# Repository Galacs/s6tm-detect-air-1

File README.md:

# S6TM Detect air 1

Air module 1 for the detect series with various co2 and mox air sensors

## IC List

- STM32F103C8T6 (Main MCU)
- HT7533 (MCU 3v3 LDO)
- HTU21D (Temperature and humidity)
- MiCS-5524 (MOX air sensor)
- S88 (CO2 NDIR sensor)
- ENS160 (MOX Sensor)
- SGP41 (MOX Sensors)
- SCD41 ("NDIR" co2 sensor)
- LMC6482 (op amp)
- SN65HVD230DR (CAN transceiver)
- LM73100 (+5V input protection)

## Top preview

## Preview 3d render

## Pin definitions

```c
#define I2C_SCL_PIN PB6
#define I2C_SDA_PIN PB7

#define RS1_PIN PA5
#define RS2_PIN PA6

#define CAN_RX_PIN PB8
#define CAN_RX_PIN  PB9

#define S88_TX_PIN PA10
#define S88_RX_PIN PA9

#define ENS160_INT_PIN PA15
```

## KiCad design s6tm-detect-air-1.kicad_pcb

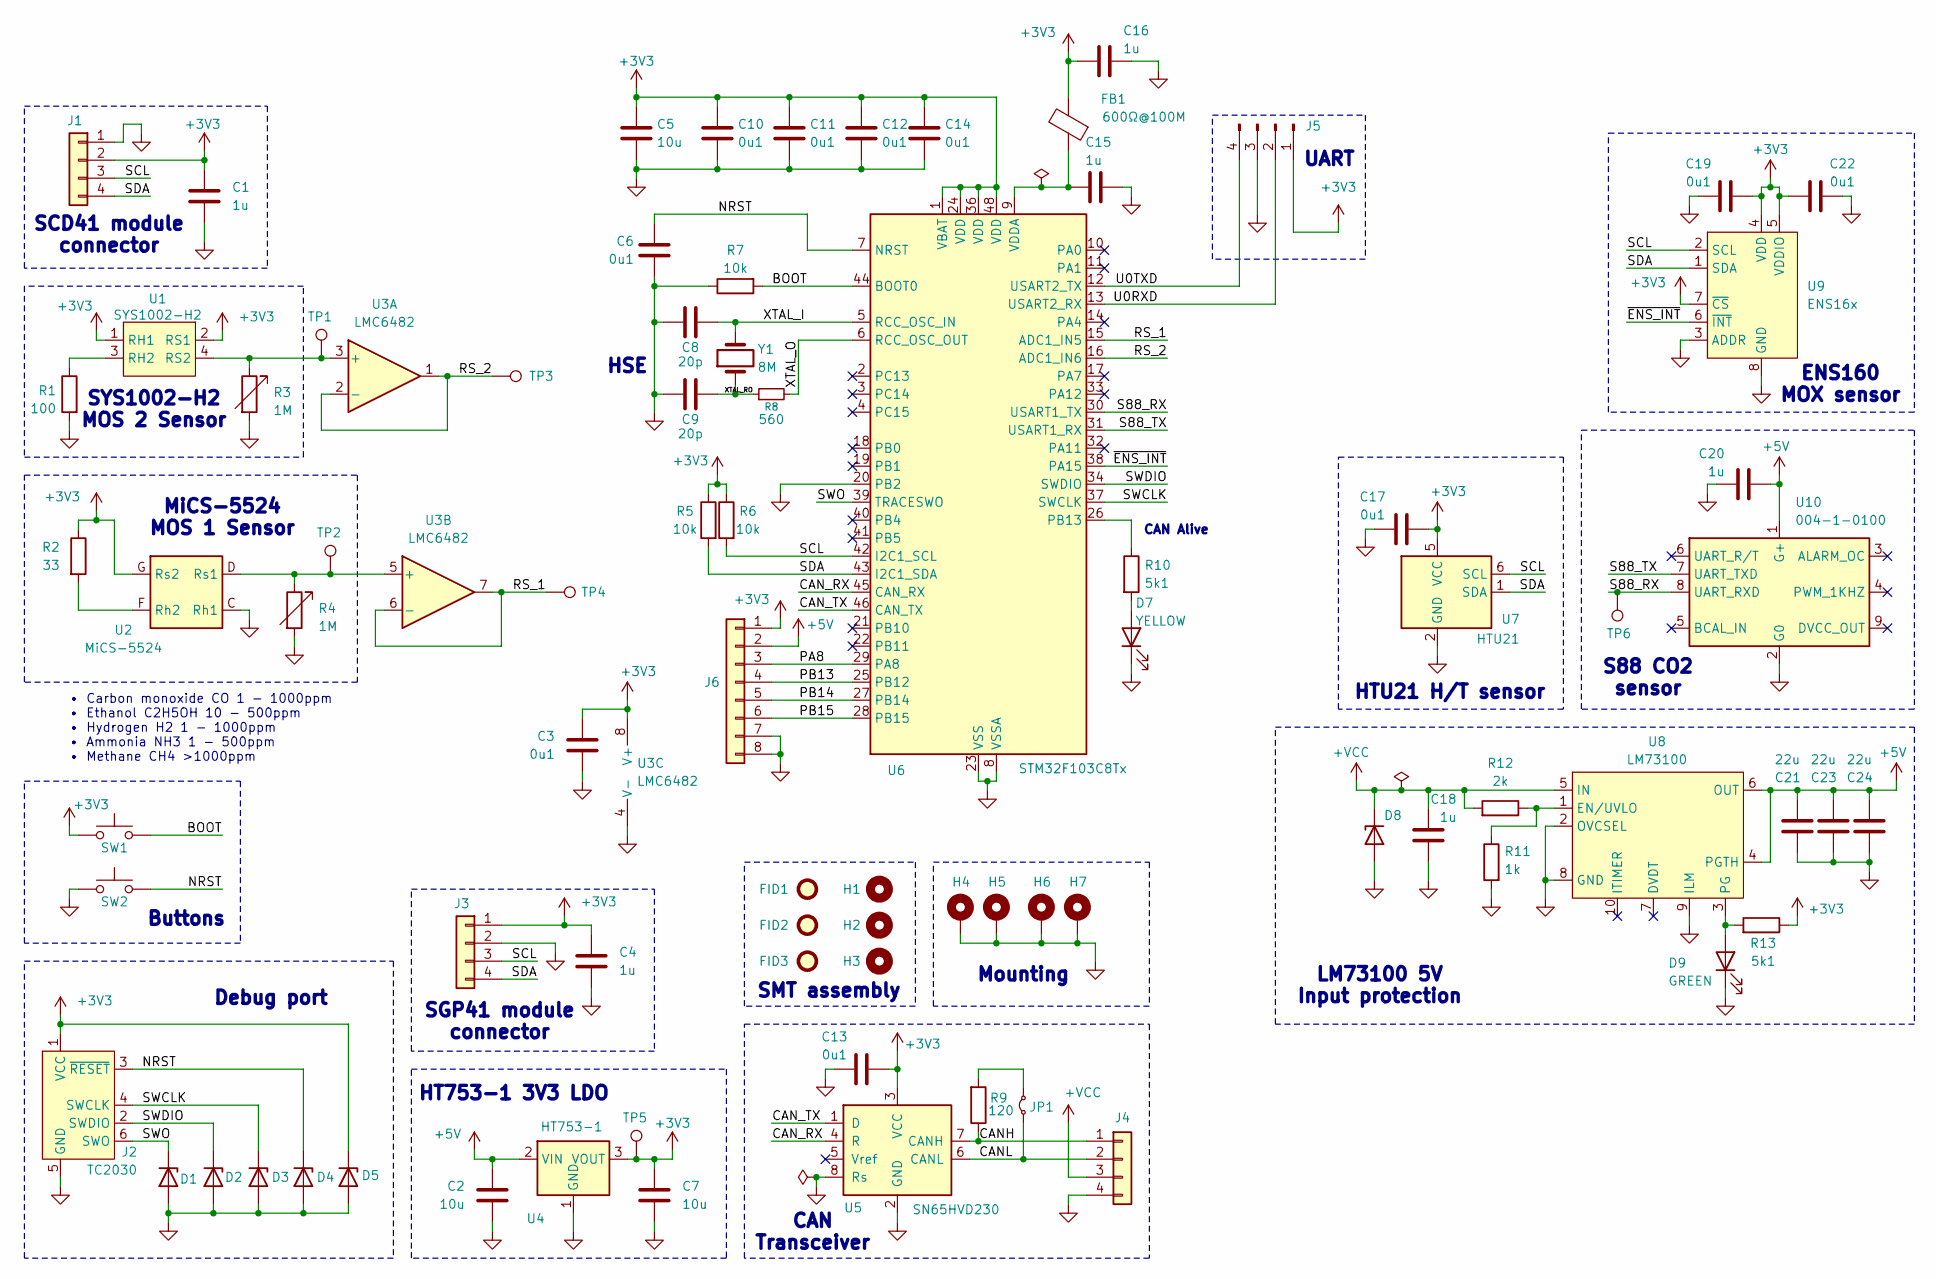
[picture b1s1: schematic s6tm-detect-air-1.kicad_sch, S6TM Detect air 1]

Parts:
C1, C4, C15, C16, C18, C20: 1u; C_0402_1005Metric; Manufacturer Part Number CL05A105KA5NQNC; JLCPCB Part # C52923
C2, C5, C7: 10u; C_0805_2012Metric; Manufacturer Part Number GRM21BR61H106KE43L; JLCPCB Part # C440198
C3, C6, C10, C11, C12, C13, C14, C17, C19, C22: 0u1; C_0402_1005Metric; Manufacturer Part Number CL05B104KB54PNC; JLCPCB Part # C307331
C8, C9: 20p; C_0603_1608Metric; Manufacturer Part Number CL10C200JB8NNNC; JLCPCB Part # C1648
C21, C23, C24: 22u; C_0805_2012Metric; Manufacturer Part Number CL21A226MAQNNNE; JLCPCB Part # C45783
D1, D2, D3, D4, D5: H5VU10U; Diode_DFN1006; Manufacturer Part Number H5VU10U; JLCPCB Part # C22395519
D7: YELLOW; LED_0805_2012Metric; Manufacturer Part Number KT-0805Y; JLCPCB Part # C2296
D8: SMAJ12A; D_SMA; Manufacturer Part Number SMAJ12A; JLCPCB Part # C19077531
D9: GREEN; LED_0805_2012Metric; Manufacturer Part Number KT-0805G; JLCPCB Part # C2297
FB1: 600Ω@100M; L_0805_2012Metric; Manufacturer Part Number MPZ2012S601ATD25; JLCPCB Part # C81034
FID1, FID2, FID3: Fiducial; Fiducial_1mm_Mask2mm
H1, H2, H3: MountingHole; ToolingHole_1.152mm
H4, H5, H6, H7: MountingHole_Pad; MountingHole_3.2mm_M3_Pad_Via
J1, J3: Conn_01x04; PinHeader_1x04_P2.54mm_Vertical
J2: TC2030; Tag-Connect_TC2030-IDC-NL_2x03_P1.27mm_Vertical
J4: Conn_01x04; JST_XH_S4B-XH-A-1_1x04_P2.50mm_Horizontal; Manufacturer Part Number S4B-XH-A-1(LF)(SN); JLCPCB Part # C163037
J5: Conn_01x04_Pin; PinHeader_1x04_P2.54mm_Vertical
J6: Conn_01x08; PinHeader_2x04_P2.54mm_Horizontal
JP1: Jumper_2_Small_Bridged; SolderJumper-2_P1.3mm_Open_RoundedPad1.0x1.5mm
R1: 100; R_0402_1005Metric; Manufacturer Part Number 0402WGF1000TCE; JLCPCB Part # C25076
R2: 33; R_0603_1608Metric; Manufacturer Part Number 0603WAF330JT5E; JLCPCB Part # C23140
R3, R4: 1M; Potentiometer_Bourns_3296W_Vertical
R5, R6, R7: 10k; R_0402_1005Metric; Manufacturer Part Number 0402WGF1002TCE; JLCPCB Part # C25744
R8: 560; R_0603_1608Metric; Manufacturer Part Number 0603WAF5600T5E; JLCPCB Part # C23204
R9: 120; R_1206_3216Metric; Manufacturer Part Number 1206W4F1200T5E; JLCPCB Part # C17909
R10, R13: 5k1; R_0402_1005Metric; Manufacturer Part Number 0402WGF5101TCE; JLCPCB Part # C25905
R11: 1k; R_0402_1005Metric; Manufacturer Part Number 0402WGF1001TCE; JLCPCB Part # C11702
R12: 2k; R_0402_1005Metric; Manufacturer Part Number 0402WGF2001TCE; JLCPCB Part # C4109
SW1, SW2: SW_Push; SW_SPST_TS-1088-xR020; Manufacturer Part Number TS-1088-AR02016; JLCPCB Part # C720477
TP1, TP2, TP3, TP4, TP5, TP6: TestPoint; TestPoint_Pad_D2.0mm
U1: SYS1002-H2; Crystal_SMD_3225-4Pin_3.2x2.5mm; Manufacturer Part Number SYS1002-H2; JLCPCB Part # C5184223
U2: MiCS-5524; Sensortech_MiCS_5x7mm_P1.25mm; Manufacturer Part Number MICS-5524; JLCPCB Part # C3659348
U3: LMC6482; SOIC-8_3.9x4.9mm_P1.27mm; Manufacturer Part Number LMC6482IMX/NOPB; JLCPCB Part # C95583
U4: HT753-1; SOT-89-3; Manufacturer Part Number HT7533-1; JLCPCB Part # C14289
U5: SN65HVD230; SOIC-8_3.9x4.9mm_P1.27mm; Manufacturer Part Number SN65HVD230DR; JLCPCB Part # C12084
U6: STM32F103C8Tx; LQFP-48_7x7mm_P0.5mm; Manufacturer Part Number STM32F103C8T6; JLCPCB Part # C8734
U7: HTU21; Texas_PWSON-N6; Manufacturer Part Number HTU21D; JLCPCB Part # C83479
U8: LM73100; Texas_RPW0010A_VQFN-HR-10_2x2mm_P0.5mm; Manufacturer Part Number LM73100RPWR; JLCPCB Part # C3210761
U9: ENS16x; Sciosense_ENS160_LGA_9_3x3mm; Manufacturer Part Number ENS160-BGLM; JLCPCB Part # C3659288
U10: 004-1-0100; Senseair_S8_Up
Y1: 8M; Crystal_SMD_5032-2Pin_5.0x3.2mm; Manufacturer Part Number X50328MSB2GI; JLCPCB Part # C115962

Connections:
+3V3: C1.2, C3.2, C4.2, C5.1, C7.1, C10.1, C11.1, C12.1, C13.1, C14.1, C16.1, C17.2, C19.1, C22.1, D5.1 (K), FB1.2, J1.2, J2.1 (VCC), J3.1, J5.1, J6.1, R2.1, R5.1, R6.1, R13.1, SW1.1, TP5.1 (1_1), U1.1 (RH1), U1.2 (RS1), U2.G (Rs2), U3.8 (V+), U4.3 (VOUT), U5.3 (VCC), U6.1 (VBAT), U6.24 (VDD), U6.36 (VDD), U6.48 (VDD), U7.5 (VCC), U9.4 (VDD), U9.5 (VDDIO), U9.7 (~CS)
+5V: C2.1, C20.1, C21.2, C23.2, C24.2, J6.2, U4.2 (VIN), U8.4 (PGTH), U8.6 (OUT), U10.1 (G+)
+VCC: C18.2, D8.1 (K), J4.3, R12.2, U8.5 (IN)
/BOOT: R7.2, SW1.2, U6.44 (BOOT0)
/CANH: J4.1, R9.1, U5.7 (CANH)
/CANL: J4.2, JP1.1 (A), U5.6 (CANL)
/CAN_RX: U5.4 (R), U6.45 (CAN_RX)
/CAN_TX: U5.1 (D), U6.46 (CAN_TX)
/NRST: C6.1, D4.1 (K), J2.3 (~RESET), SW2.2, U6.7 (NRST)
/PA8: J6.3, U6.29 (PA8)
/PB13: J6.4, U6.25 (PB12)
/PB14: J6.5, U6.27 (PB14)
/PB15: J6.6, U6.28 (PB15)
/RS_1: TP4.1 (1_1), U3.6 (-), U3.7, U6.15 (ADC1_IN5)
/RS_2: TP3.1 (1_1), U3.1, U3.2 (-), U6.16 (ADC1_IN6)
/S88_RX: TP6.1 (1_1), U6.30 (USART1_TX), U10.8 (UART_RXD)
/S88_TX: U6.31 (USART1_RX), U10.7 (UART_TXD)
/SCL: J1.3, J3.3, R6.2, U6.42 (I2C1_SCL), U7.6 (SCL), U9.2 (SCL)
/SDA: J1.4, J3.4, R5.2, U6.43 (I2C1_SDA), U7.1 (SDA), U9.1 (SDA)
/SWCLK: D3.1 (K), J2.4 (SWCLK), U6.37 (SWCLK)
/SWDIO: D2.1 (K), J2.2 (SWDIO), U6.34 (SWDIO)
/SWO: D1.1 (K), J2.6 (SWO), U6.39 (TRACESWO)
/U0RXD: J5.2, U6.13 (USART2_RX)
/U0TXD: J5.4, U6.12 (USART2_TX)
/XTAL_I: C8.1, U6.5 (RCC_OSC_IN), Y1.2
/XTAL_O: R8.2, U6.6 (RCC_OSC_OUT)
/XTAL_RO: C9.1, R8.1, Y1.1
/~ENS_INT: U6.38 (PA15), U9.6 (~INT)
GND: C1.1, C2.2, C3.1, C4.1, C5.2, C6.2, C7.2, C8.2, C9.2, C10.2, C11.2, C12.2, C13.2, C14.2, C15.2, C16.2, C17.1, C18.1, C19.2, C20.2, C21.1, C22.2, C23.1, C24.1, D1.2 (A), D2.2 (A), D3.2 (A), D4.2 (A), D5.2 (A), D7.1 (K), D8.2 (A), D9.1 (K), H4.1 (1_1), H5.1 (1_1), H6.1 (1_1), H7.1 (1_1), J1.1, J2.5 (GND), J3.2, J4.4, J5.3, J6.7, J6.8, R1.2, R3.2, R4.2, R7.1, R11.2, SW2.1, U2.C (Rh1), U3.4 (V-), U4.1 (GND), U5.2 (GND), U5.8 (Rs), U6.8 (VSSA), U6.20 (PB2), U6.23 (VSS), U6.35 (VSS), U6.47 (VSS), U7.2 (GND), U8.2 (OVCSEL), U8.8 (GND), U8.9 (ILM), U9.3 (ADDR), U9.8 (GND), U9.9 (GND), U10.2 (G0)
unnamed: D7.2 (A), R10.2
unnamed: D9.2 (A), R13.2, U8.3 (PG)
unnamed: JP1.2 (B), R9.2
unnamed: R1.1, U1.3 (RH2)
unnamed: R3.1, TP1.1 (1_1), U1.4 (RS2), U3.3 (+)
unnamed: R2.2, U2.F (Rh2)
unnamed: R4.1, TP2.1 (1_1), U2.D (Rs1), U3.5 (+)
unnamed: R10.1, U6.26 (PB13)
unnamed: C15.1, FB1.1, U6.9 (VDDA)
unnamed: R11.1, R12.1, U8.1 (EN/UVLO)

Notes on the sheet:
CAN Transceiver
SCD41 module connector
Mounting
SYS1002-H2 MOS 2 Sensor
SMT assembly
MiCS-5524 MOS 1 Sensor
HTU21 H/T sensor
LM73100 5V Input protection
Buttons
SGP41 module connector
UART
• Carbon monoxide CO 1 - 1000ppm • Ethanol C2H5OH 10 - 500ppm • Hydrogen H2 1 - 1000ppm • Ammonia NH3 1 - 500ppm • Methane CH4 >1000ppm
HSE
ENS160 MOX sensor
S88 CO2 sensor
CAN Alive
Debug port
HT753-1 3V3 LDO

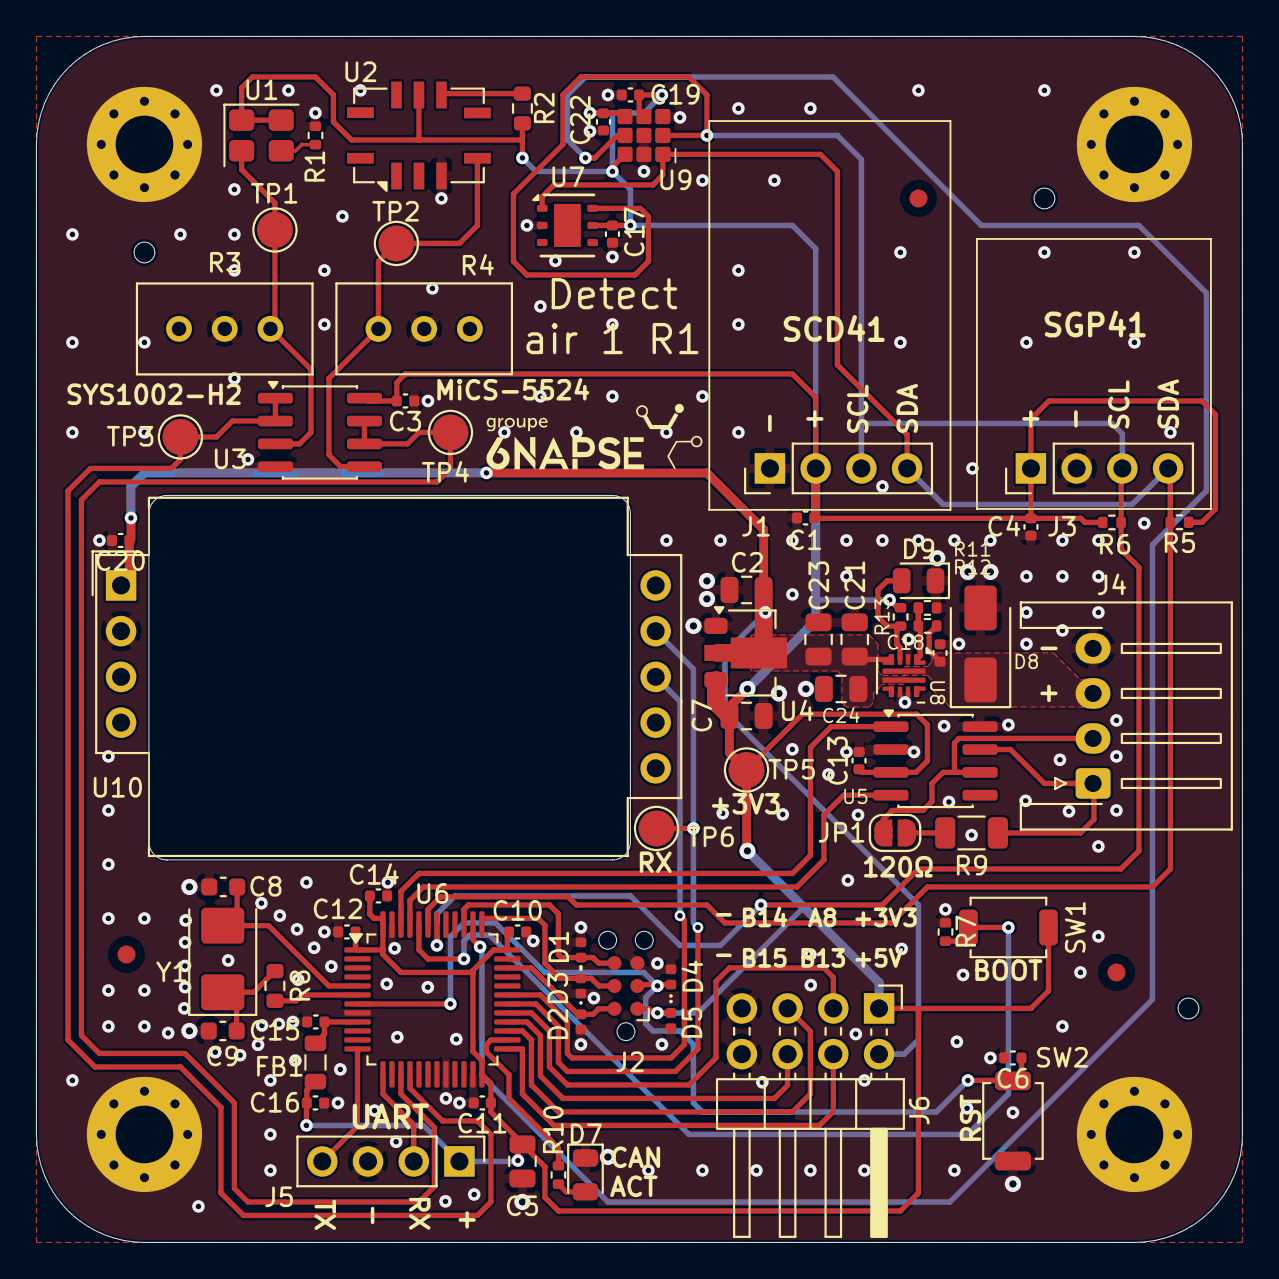
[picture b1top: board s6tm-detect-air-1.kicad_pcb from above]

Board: 2 copper layers, 67.0 x 67.0 mm, 82 parts (0 on the bottom side), 39 nets.

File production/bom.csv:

Designator,Footprint,Quantity,Value,LCSC Part #
"C1, C15, C16, C18, C20, C4",0402,6,1u,C52923
"C10, C11, C12, C13, C14, C17, C19, C22, C3, C6",0402,10,0u1,C307331
"C2, C5, C7",0805,3,10u,C440198
"C21, C23, C24",0805,3,22u,C45783
"C8, C9",0603,2,20p,C1648
"D1, D2, D3, D4, D5",Diode_DFN1006,5,H5VU10U,C22395519
D7,0805,1,YELLOW,C2296
D8,D_SMA,1,SMAJ12A,C19077531
D9,0805,1,GREEN,C2297
FB1,0805,1,600Ω@100M,C81034
J6,PinHeader_2x04_P2.54mm_Horizontal,1,Conn_01x08,
R1,0402,1,100,C25076
"R10, R13",0402,2,5k1,C25905
R11,0402,1,1k,C11702
R12,0402,1,2k,C4109
R2,0603,1,33,C23140
"R5, R6, R7",0402,3,10k,C25744
R8,0603,1,560,C23204
R9,1206,1,120,C17909
"SW1, SW2",SW_SPST_TS-1088-xR020,2,SW_Push,C720477
U1,Crystal_SMD_3225-4Pin_3.2x2.5mm,1,SYS1002-H2,C5184223
U2,Sensortech_MiCS_5x7mm_P1.25mm,1,MiCS-5524,C3659348
U3,SOIC-8_3.9x4.9mm_P1.27mm,1,LMC6482,C95583
U4,SOT-89-3,1,HT753-1,C14289
U5,SOIC-8_3.9x4.9mm_P1.27mm,1,SN65HVD230,C12084
U6,LQFP-48_7x7mm_P0.5mm,1,STM32F103C8Tx,C8734
U7,Texas_PWSON-N6,1,HTU21,C83479
U8,Texas_RPW0010A_VQFN-HR-10_2x2mm_P0.5mm,1,LM73100,C3210761
U9,Sciosense_ENS160_LGA_9_3x3mm,1,ENS16x,C3659288
Y1,Crystal_SMD_5032-2Pin_5.0x3.2mm,1,8M,C115962
